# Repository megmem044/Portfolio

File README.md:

# Tic Tac Toe (Java)

A console based Tic Tac Toe game implemented using pure Java.  
The project follows a clean separation of concerns and includes basic tests without external frameworks.

## Features
- Two player console gameplay
- Turn based move handling
- Win detection for rows, columns, and diagonals
- Draw detection
- Board state rendering in console
- Reset and replay support
- Simple test coverage for core game logic

## Project Structure

tictactoe/
├── src/
│ └── com/app/tictactoe/
│ ├── Main.java
│ ├── Game.java
│ ├── Board.java
│ ├── Player.java
│ └── ConsoleUI.java
└── test/
└── com/app/tictactoe/
├── BoardTest.java
└── GameTest.java

## How to Compile

From the project root directory:
javac -d out src/com/app/tictactoe/.java test/com/app/tictactoe/.java

## How to Run Tests
java -cp out com.app.tictactoe.BoardTest
java -cp out com.app.tictactoe.GameTest

## How to Run the Game
java -cp out com.app.tictactoe.Main

## Notes
- No external libraries or frameworks are used
- Tests are written using plain Java assertions
- The project is structured to be easily extensible

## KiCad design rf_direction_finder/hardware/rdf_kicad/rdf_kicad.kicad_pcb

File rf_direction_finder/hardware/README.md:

# Hardware

This directory contains KiCAD hardware design files for the RF Direction Finder.

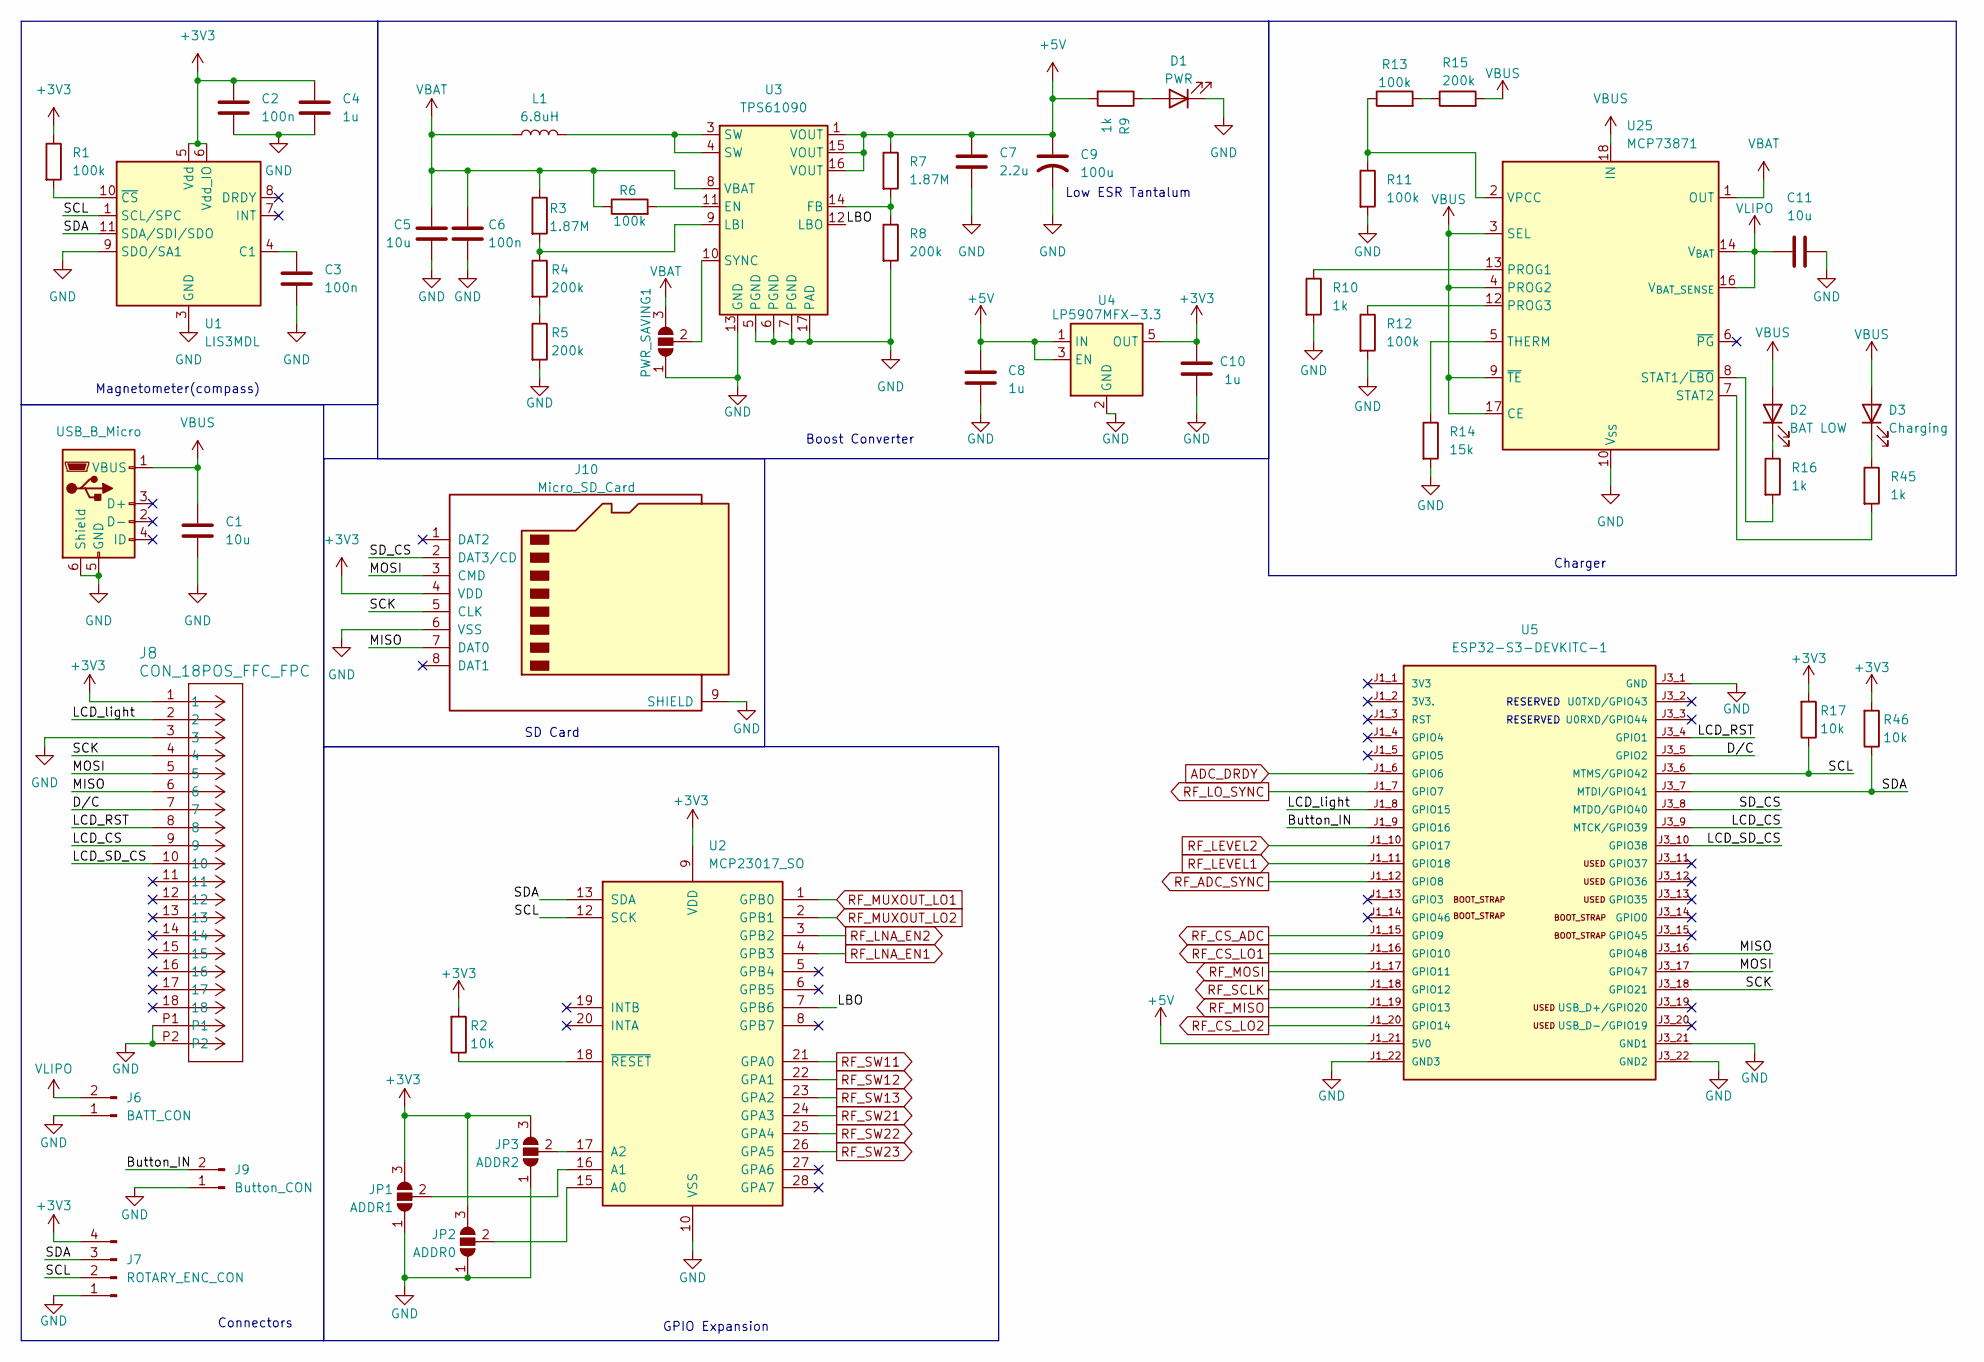
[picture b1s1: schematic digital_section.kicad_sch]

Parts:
C1, C5, C11: 10u; C_0603_1608Metric_Pad1.08x0.95mm_HandSolder
C2, C3, C6: 100n; C_0603_1608Metric_Pad1.08x0.95mm_HandSolder
C4, C8, C10: 1u; C_0603_1608Metric_Pad1.08x0.95mm_HandSolder
C7: 2.2u; C_0603_1608Metric_Pad1.08x0.95mm_HandSolder
C9: 100u; CP_EIA-3528-15_AVX-H_HandSolder
D1: PWR; LED_0603_1608Metric_Pad1.05x0.95mm_HandSolder
D2: BAT LOW; LED_0603_1608Metric_Pad1.05x0.95mm_HandSolder
D3: Charging; LED_0603_1608Metric_Pad1.05x0.95mm_HandSolder
J5: USB_B_Micro; USB_Micro-B_Amphenol_10118194-0001LF_Horizontal
J6: BATT_CON; PinHeader_1x02_P2.54mm_Vertical
J7: ROTARY_ENC_CON; PinHeader_1x04_P2.54mm_Vertical
J8: CON_18POS_FFC_FPC; CON_5051101892_MOL; Mfr_part 5051101892
J9: Button_CON; PinHeader_1x02_P2.54mm_Vertical
J10: Micro_SD_Card; microSD_HC_Molex_47219-2001
JP1: ADDR1; SolderJumper-3_P1.3mm_Open_RoundedPad1.0x1.5mm_NumberLabels
JP2: ADDR0; SolderJumper-3_P1.3mm_Open_RoundedPad1.0x1.5mm_NumberLabels
JP3: ADDR2; SolderJumper-3_P1.3mm_Open_RoundedPad1.0x1.5mm_NumberLabels
L1: 6.8uH; L_Sunlord_MWSA0412S
PWR_SAVING1: SolderJumper_3_Open; SolderJumper-3_P1.3mm_Open_RoundedPad1.0x1.5mm_NumberLabels
R1, R6, R11, R12, R13: 100k; R_0603_1608Metric_Pad0.98x0.95mm_HandSolder
R2, R17, R46: 10k; R_0603_1608Metric_Pad0.98x0.95mm_HandSolder
R3, R7: 1.87M; R_0603_1608Metric_Pad0.98x0.95mm_HandSolder
R4, R5, R8, R15: 200k; R_0603_1608Metric_Pad0.98x0.95mm_HandSolder
R9, R10, R16, R45: 1k; R_0603_1608Metric_Pad0.98x0.95mm_HandSolder
R14: 15k; R_0603_1608Metric_Pad0.98x0.95mm_HandSolder
U1: LIS3MDL; LGA-12_2x2mm_P0.5mm
U2: MCP23017_SO; SOIC-28W_7.5x17.9mm_P1.27mm
U3: TPS61090; Texas_RSA_VQFN-16-1EP_4x4mm_P0.65mm_EP2.7x2.7mm_ThermalVias
U4: LP5907MFX-3.3; SOT-23-5
U5: ESP32-S3-DEVKITC-1; ESP32-S3-DEVKITC-1-N8R8
U25: MCP73871; QFN-20-1EP_4x4mm_P0.5mm_EP2.5x2.5mm

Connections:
+3V3: C2.2, C4.2, C10.2, J7.4, J8.1, J10.4 (VDD), JP1.3 (B), JP2.3 (B), JP3.3 (B), R1.1, R2.2, R17.2, R46.2, U1.5 (Vdd), U1.6 (Vdd_IO), U2.9 (VDD), U4.5 (OUT); also elsewhere on the board
+5V: C7.2, C8.2, C9.1, R7.1, R9.2, U3.1 (VOUT), U3.15 (VOUT), U3.16 (VOUT), U4.1 (IN), U4.3 (EN), U5.J1_21 (5V0); also elsewhere on the board
/Digital Section/Button_IN: J9.2, U5.J1_9 (GPIO16)
/Digital Section/D/C: J8.7, U5.J3_5 (GPIO2)
/Digital Section/LBO: U2.7 (GPB6), U3.12 (LBO)
/Digital Section/LCD_CS: J8.9, U5.J3_9 (MTCK/GPIO39)
/Digital Section/LCD_RST: J8.8, U5.J3_4 (GPIO1)
/Digital Section/LCD_SD_CS: J8.10, U5.J3_10 (GPIO38)
/Digital Section/LCD_light: J8.2, U5.J1_8 (GPIO15)
/Digital Section/MISO: J8.6, J10.7 (DAT0), U5.J3_16 (GPIO48)
/Digital Section/MOSI: J8.5, J10.3 (CMD), U5.J3_17 (GPIO47)
/Digital Section/SCK: J8.4, J10.5 (CLK), U5.J3_18 (GPIO21)
/Digital Section/SCL: J7.2, R17.1, U1.1 (SCL/SPC), U2.12 (SCK), U5.J3_6 (MTMS/GPIO42)
/Digital Section/SDA: J7.3, R46.1, U1.11 (SDA/SDI/SDO), U2.13 (SDA), U5.J3_7 (MTDI/GPIO41)
/Digital Section/SD_CS: J10.2 (DAT3/CD), U5.J3_8 (MTDO/GPIO40)
ADC_DRDY: U5.J1_6 (GPIO6); also elsewhere on the board
GND: C1.1, C2.1, C3.1, C4.1, C5.1, C6.1, C7.1, C8.1, C9.2, C10.1, C11.1, D1.1 (K), J5.5 (GND), J5.6 (Shield), J6.1, J7.1, J8.3, J8.P1, J8.P2, J9.1, J10.6 (VSS), J10.9 (SHIELD), JP1.1 (A), JP2.1 (A), JP3.1 (A), PWR_SAVING1.1 (A), R5.2, R8.2, R10.2, R11.2, R12.2, R14.2, U1.2 (GND), U1.3 (GND), U1.9 (SDO/SA1), U1.12 (GND), U2.10 (VSS), U3.5 (PGND), U3.6 (PGND), U3.7 (PGND), U3.13 (GND), U3.17 (PAD), U4.2 (GND), U5.J1_22 (GND3), U5.J3_1 (GND), U5.J3_21 (GND1), U5.J3_22 (GND2), U25.10 (V_{SS}), U25.11 (V_{SS}), U25.21 (V_{SS}); also elsewhere on the board
unnamed: D1.2 (A), R9.1
unnamed: D2.1 (K), R16.1
unnamed: D3.1 (K), R45.1
unnamed: JP1.2 (C), U2.16 (A1)
unnamed: JP2.2 (C), U2.15 (A0)
unnamed: JP3.2 (C), U2.17 (A2)
unnamed: L1.2, U3.3 (SW), U3.4 (SW)
unnamed: PWR_SAVING1.2 (C), U3.10 (SYNC)
unnamed: R4.2, R5.1
unnamed: R13.2, R15.1
unnamed: C3.2, U1.4 (C1)
unnamed: R1.2, U1.10 (~CS)
unnamed: R2.1, U2.18 (~RESET)
unnamed: R6.2, U3.11 (EN)
unnamed: R7.2, R8.1, U3.14 (FB)
unnamed: R3.2, R4.1, U3.9 (LBI)
unnamed: R10.1, U25.13 (PROG1)
unnamed: R12.1, U25.12 (PROG3)
unnamed: R16.2, U25.8 (STAT1/~LBO)
unnamed: R45.2, U25.7 (STAT2)
unnamed: R14.1, U25.5 (THERM)
unnamed: R11.1, R13.1, U25.2 (VPCC)
RF_ADC_SYNC: U5.J1_12 (GPIO8); also elsewhere on the board
RF_CS_ADC: U5.J1_15 (GPIO9); also elsewhere on the board
RF_CS_LO1: U5.J1_16 (GPIO10); also elsewhere on the board
RF_CS_LO2: U5.J1_20 (GPIO14); also elsewhere on the board
RF_LEVEL1: U5.J1_11 (GPIO18); also elsewhere on the board
RF_LEVEL2: U5.J1_10 (GPIO17); also elsewhere on the board
RF_LNA_EN1: U2.4 (GPB3); also elsewhere on the board
RF_LNA_EN2: U2.3 (GPB2); also elsewhere on the board
RF_LO_SYNC: U5.J1_7 (GPIO7); also elsewhere on the board
RF_MISO: U5.J1_19 (GPIO13); also elsewhere on the board
RF_MOSI: U5.J1_17 (GPIO11); also elsewhere on the board
RF_MUXOUT_LO1: U2.1 (GPB0); also elsewhere on the board
RF_MUXOUT_LO2: U2.2 (GPB1); also elsewhere on the board
RF_SCLK: U5.J1_18 (GPIO12); also elsewhere on the board
RF_SW11: U2.21 (GPA0); also elsewhere on the board
RF_SW12: U2.22 (GPA1); also elsewhere on the board
RF_SW13: U2.23 (GPA2)
RF_SW21: U2.24 (GPA3); also elsewhere on the board
RF_SW22: U2.25 (GPA4); also elsewhere on the board
RF_SW23: U2.26 (GPA5)
VBAT: C5.2, C6.2, L1.1, PWR_SAVING1.3 (B), R3.1, R6.1, U3.8 (VBAT), U25.1 (OUT), U25.20 (OUT)
VBUS: C1.2, D2.2 (A), D3.2 (A), J5.1 (VBUS), R15.2, U25.3 (SEL), U25.4 (PROG2), U25.9 (~TE), U25.17 (CE), U25.18 (IN), U25.19 (IN)
VLIPO: C11.2, J6.2, U25.14 (V_{BAT}), U25.15 (V_{BAT}), U25.16 (V_{BAT_SENSE})

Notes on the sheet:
Boost Converter
RESERVED
Connectors
Charger
SD Card
Magnetometer(compass)
Low ESR Tantalum
GPIO Expansion

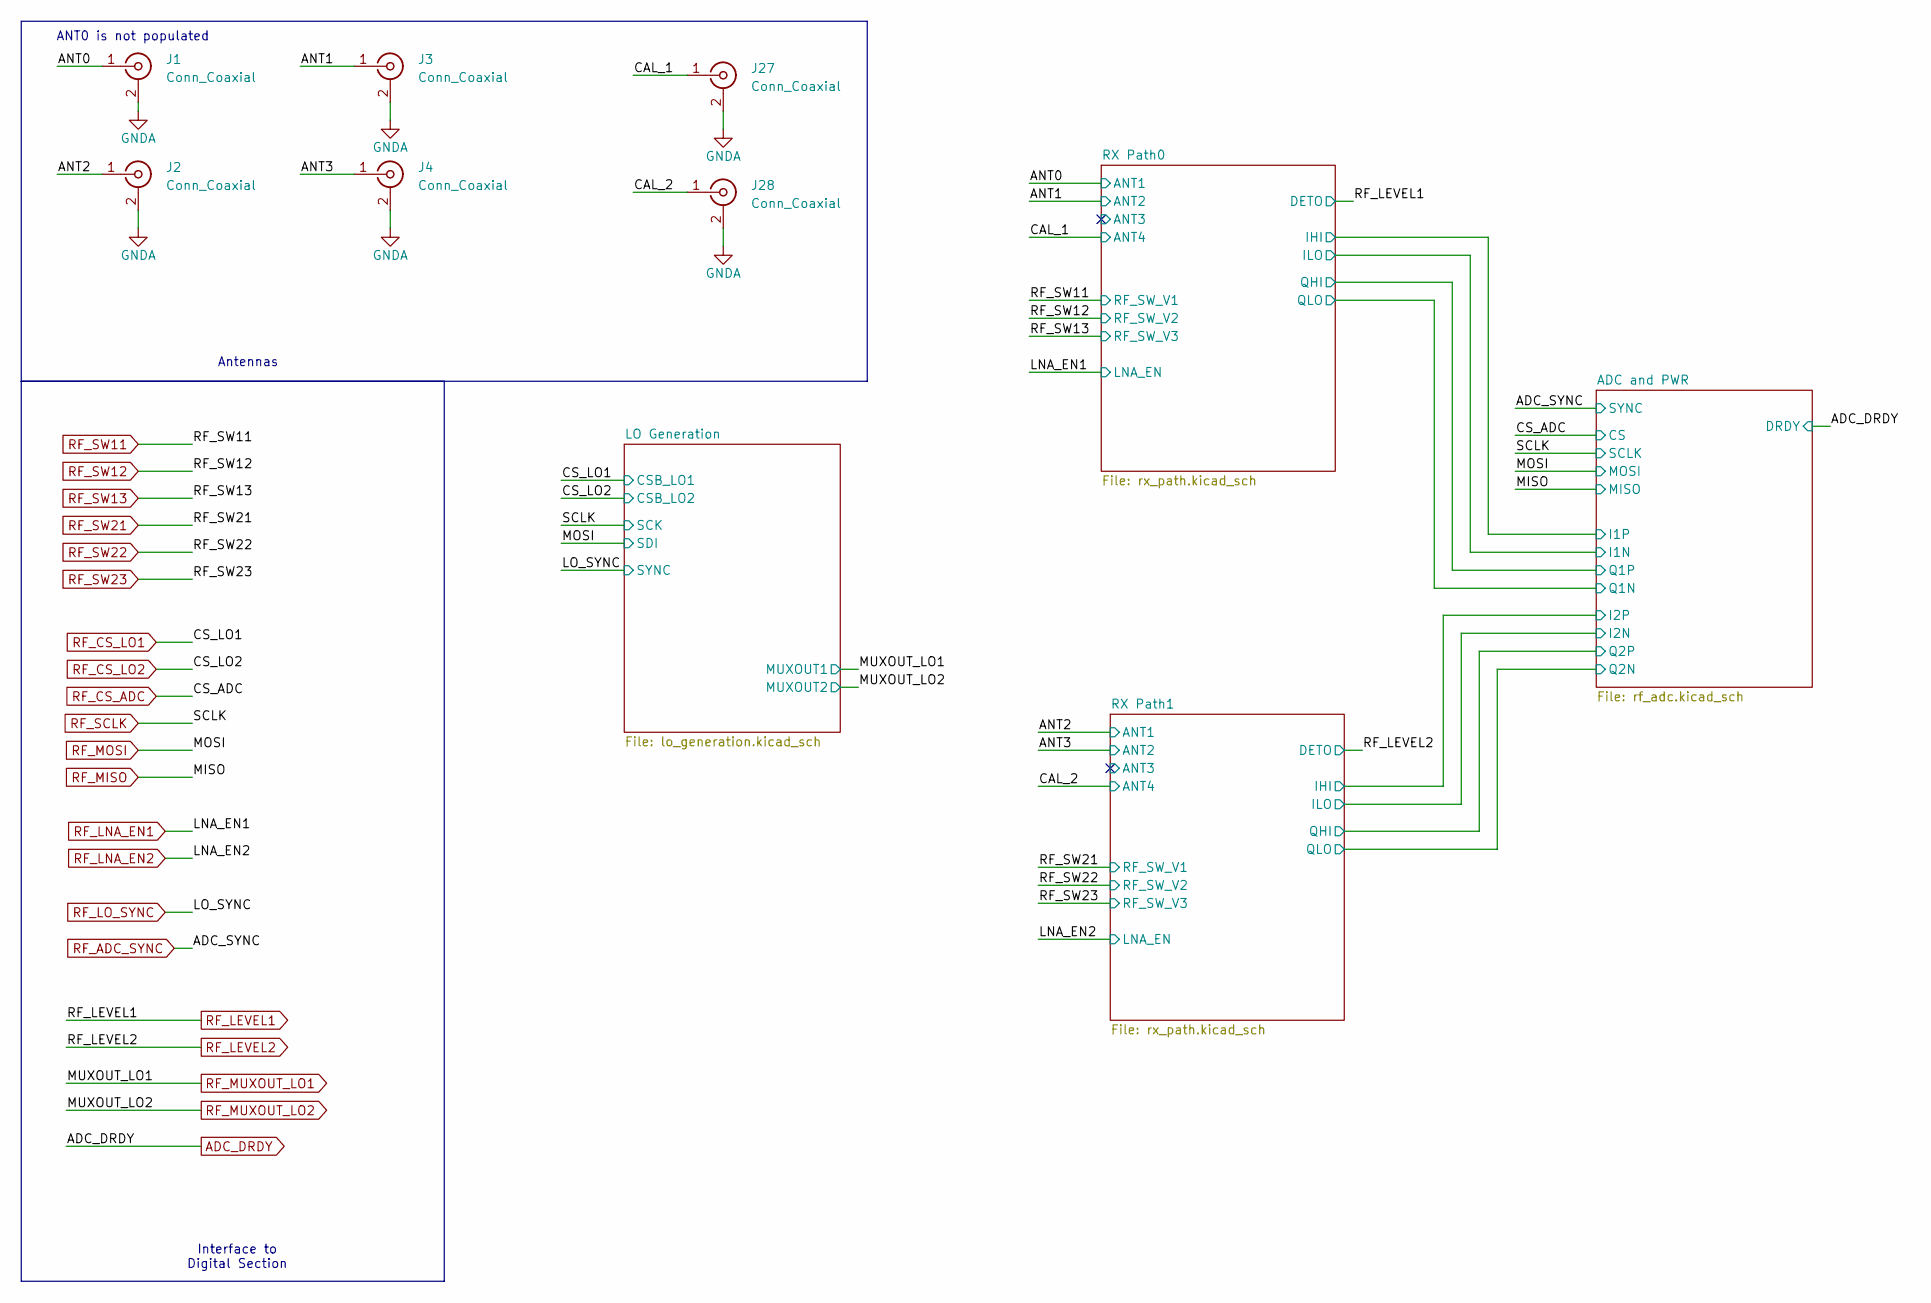
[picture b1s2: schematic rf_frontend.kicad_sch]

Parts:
J1, J2, J3, J4, J27, J28: Conn_Coaxial; U.FL_Molex_MCRF_73412-0110_Vertical

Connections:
/RF Frontend/ANT0: J1.1 (In); also elsewhere on the board
/RF Frontend/ANT1: J3.1 (In); also elsewhere on the board
/RF Frontend/ANT2: J2.1 (In); also elsewhere on the board
/RF Frontend/ANT3: J4.1 (In); also elsewhere on the board
/RF Frontend/CAL_1: J27.1 (In); also elsewhere on the board
/RF Frontend/CAL_2: J28.1 (In); also elsewhere on the board
GND: J1.2 (Ext), J2.2 (Ext), J3.2 (Ext), J4.2 (Ext), J27.2 (Ext), J28.2 (Ext); also elsewhere on the board

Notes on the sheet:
Antennas
Interface to Digital Section
ANT0 is not populated

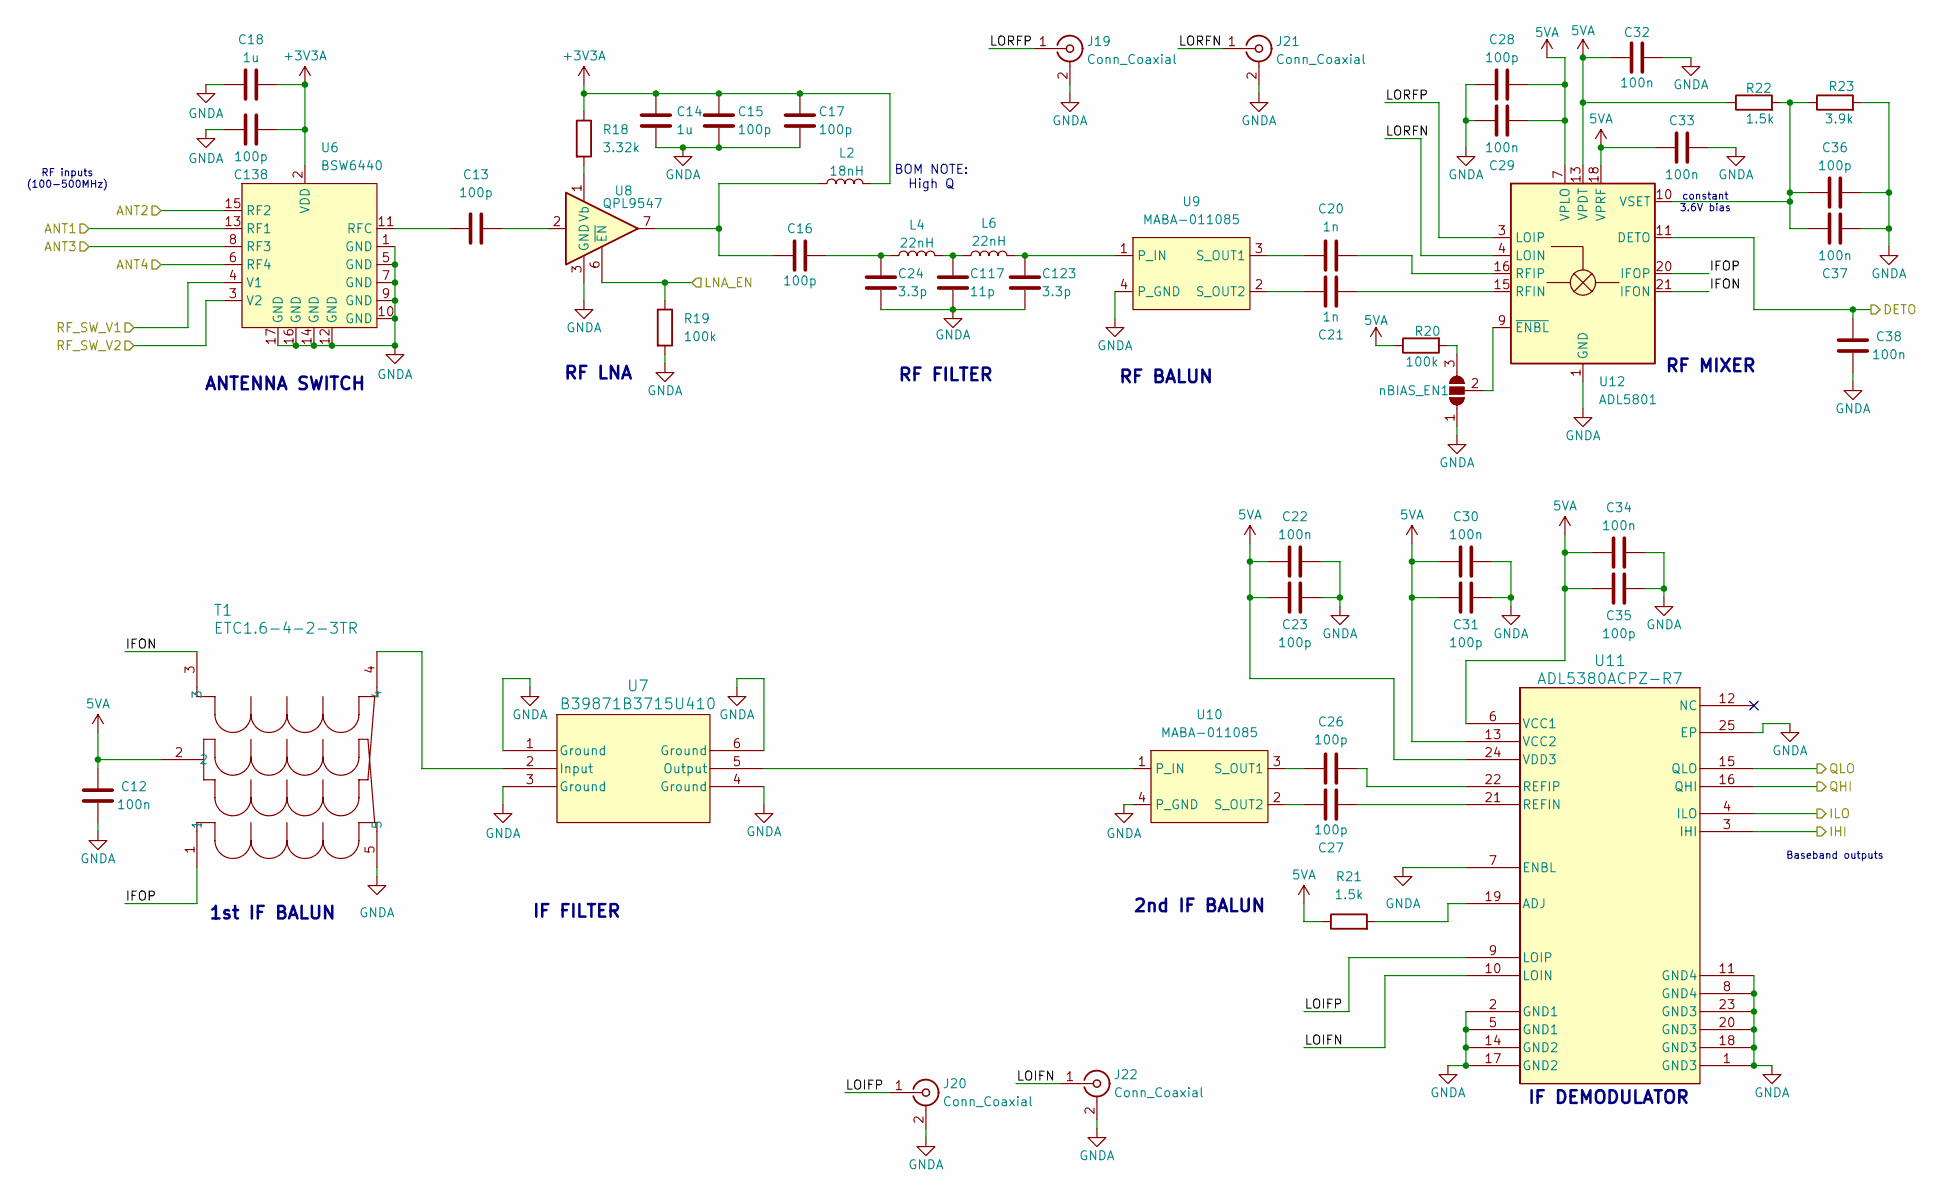
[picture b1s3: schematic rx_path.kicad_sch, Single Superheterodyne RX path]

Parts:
C12, C22, C29, C30, C32, C33, C34, C37, C38: 100n; C_0603_1608Metric_Pad1.08x0.95mm_HandSolder
C13, C16, C26, C27: 100p; C_0402_1005Metric
C14, C18: 1u; C_0603_1608Metric_Pad1.08x0.95mm_HandSolder
C15, C17, C23, C28, C31, C35, C36, C138: 100p; C_0603_1608Metric_Pad1.08x0.95mm_HandSolder
C20, C21: 1n; C_0402_1005Metric
C24, C123: 3.3p; C_0402_1005Metric
C117: 11p; C_0402_1005Metric
J19, J20, J21, J22: Conn_Coaxial; U.FL_Molex_MCRF_73412-0110_Vertical
L2: 18nH; L_0402_1005Metric
L4, L6: 22nH; L_0402_1005Metric
R18: 3.32k; R_0603_1608Metric_Pad0.98x0.95mm_HandSolder
R19, R20: 100k; R_0603_1608Metric_Pad0.98x0.95mm_HandSolder
R21, R22: 1.5k; R_0603_1608Metric_Pad0.98x0.95mm_HandSolder
R23: 3.9k; R_0603_1608Metric_Pad0.98x0.95mm_HandSolder
T1: ETC1.6-4-2-3TR; ETC1.6-4-2-3TR_MCM
U6: BSW6440
U7: B39871B3715U410
U8: QPL9547; DFN-8-1EP_2x2mm_P0.5mm_EP0.8x1.6mm
U9, U10: MABA-011085; SMD-4P_7.1x6.4mm
U11: ADL5380ACPZ-R7
U12: ADL5801; ADL5801_LFCSP-VQ-24-1EP_4x4mm_P0.5mm_EP2.642x2.642mm
nBIAS_EN1: SolderJumper_3_Open; SolderJumper-3_P1.3mm_Open_RoundedPad1.0x1.5mm_NumberLabels

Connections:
+3V3A: C14.2, C15.2, C17.2, C18.2, C138.2, L2.2, R18.1, U6.2 (VDD); also elsewhere on the board
+5VA: C12.2, C22.2, C23.2, C28.2, C29.2, C30.2, C31.2, C32.1, C33.1, C34.2, C35.2, R20.1, R21.1, R22.1, T1.2, U11.6 (VCC1), U11.13 (VCC2), U11.24 (VDD3), U12.7 (VPLO), U12.13 (VPDT), U12.18 (VPRF), U12.24 (VPLO); also elsewhere on the board
/RF Frontend/ADC and PWR/I1N: U11.4 (ILO); also elsewhere on the board
/RF Frontend/ADC and PWR/I1P: U11.3 (IHI); also elsewhere on the board
/RF Frontend/ADC and PWR/Q1N: U11.15 (QLO); also elsewhere on the board
/RF Frontend/ADC and PWR/Q1P: U11.16 (QHI); also elsewhere on the board
/RF Frontend/ANT0: U6.13 (RF1); also elsewhere on the board
/RF Frontend/ANT1: U6.15 (RF2); also elsewhere on the board
/RF Frontend/CAL_1: U6.6 (RF4); also elsewhere on the board
/RF Frontend/RX Path0/ANT3: U6.8 (RF3)
/RF Frontend/RX Path0/IFON: T1.3, U12.21 (IFON)
/RF Frontend/RX Path0/IFOP: T1.1, U12.20 (IFOP)
/RF Frontend/RX Path0/LOIFN: J22.1 (In), U11.10 (LOIN)
/RF Frontend/RX Path0/LOIFP: J20.1 (In), U11.9 (LOIP)
/RF Frontend/RX Path0/LORFN: J21.1 (In), U12.4 (LOIN)
/RF Frontend/RX Path0/LORFP: J19.1 (In), U12.3 (LOIP)
GND: C12.1, C14.1, C15.1, C17.1, C18.1, C22.1, C23.1, C24.2, C28.1, C29.1, C30.1, C31.1, C32.2, C33.2, C34.1, C35.1, C36.1, C37.1, C38.1, C117.2, C123.2, C138.1, J19.2 (Ext), J20.2 (Ext), J21.2 (Ext), J22.2 (Ext), R19.2, R23.2, T1.5, U6.1 (GND), U6.5 (GND), U6.7 (GND), U6.9 (GND), U6.10 (GND), U6.12 (GND), U6.14 (GND), U6.16 (GND), U6.17 (GND), U7.1 (Ground), U7.3 (Ground), U7.4 (Ground), U7.6 (Ground), U8.3 (GND), U8.4 (GND), U8.5 (GND), U8.8 (GND), U8.9 (GND), U9.4 (P_GND), U10.4 (P_GND), U11.1 (GND3), U11.2 (GND1), U11.5 (GND1), U11.7 (ENBL), U11.8 (GND4), U11.11 (GND4), U11.14 (GND2), U11.17 (GND2), U11.18 (GND3), U11.20 (GND3), U11.23 (GND3), U11.25 (EP), U12.1 (GND), U12.2 (GND), U12.5 (GND), U12.6 (GND), U12.8 (GND), U12.12 (GND), U12.14 (GND), U12.17 (GND), U12.19 (GND), U12.23 (GND), U12.25 (GND), nBIAS_EN1.1 (A); also elsewhere on the board
unnamed: C13.2, U8.2
unnamed: C16.1, L2.1, U8.7
unnamed: C16.2, C24.1, L4.1
unnamed: C117.1, L4.2, L6.1
unnamed: C13.1, U6.11 (RFC)
unnamed: T1.4, U7.2 (Input)
unnamed: R18.2, U8.1 (Vb)
unnamed: C123.1, L6.2, U9.1 (P_IN)
unnamed: C20.1, U9.3 (S_OUT1)
unnamed: C21.2, U9.2 (S_OUT2)
unnamed: U7.5 (Output), U10.1 (P_IN)
unnamed: C26.1, U10.3 (S_OUT1)
unnamed: C27.2, U10.2 (S_OUT2)
unnamed: R21.2, U11.19 (ADJ)
unnamed: C27.1, U11.21 (REFIN)
unnamed: C26.2, U11.22 (REFIP)
unnamed: C21.1, U12.15 (RFIN)
unnamed: C20.2, U12.16 (RFIP)
unnamed: C36.2, C37.2, R22.2, R23.1, U12.10 (VSET)
unnamed: U12.9 (~ENBL), nBIAS_EN1.2 (C)
unnamed: R20.2, nBIAS_EN1.3 (B)
RF_LEVEL1: C38.2, U12.11 (DETO); also elsewhere on the board
RF_LNA_EN1: R19.1, U8.6 (~EN); also elsewhere on the board
RF_SW11: U6.4 (V1); also elsewhere on the board
RF_SW12: U6.3 (V2); also elsewhere on the board

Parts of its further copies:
C19, C113: 1u; C_0603_1608Metric_Pad1.08x0.95mm_HandSolder
C25, C124: 3.3p; C_0402_1005Metric
C111, C121, C128, C129, C131, C132, C133, C136, C137: 100n; C_0603_1608Metric_Pad1.08x0.95mm_HandSolder
C112, C115, C125, C126: 100p; C_0402_1005Metric
C114, C116, C122, C127, C130, C134, C135, C139: 100p; C_0603_1608Metric_Pad1.08x0.95mm_HandSolder
C118: 11p; C_0402_1005Metric
C119, C120: 1n; C_0402_1005Metric
J23, J24, J25, J26: Conn_Coaxial; U.FL_Molex_MCRF_73412-0110_Vertical
L3: 18nH; L_0402_1005Metric
L5, L7: 22nH; L_0402_1005Metric
R39: 3.32k; R_0603_1608Metric_Pad0.98x0.95mm_HandSolder
R40, R41: 100k; R_0603_1608Metric_Pad0.98x0.95mm_HandSolder
R42, R43: 1.5k; R_0603_1608Metric_Pad0.98x0.95mm_HandSolder
R44: 3.9k; R_0603_1608Metric_Pad0.98x0.95mm_HandSolder
T2: ETC1.6-4-2-3TR; ETC1.6-4-2-3TR_MCM
U18: BSW6440
U19: B39871B3715U410
U20: QPL9547; DFN-8-1EP_2x2mm_P0.5mm_EP0.8x1.6mm
U21, U22: MABA-011085; SMD-4P_7.1x6.4mm
U23: ADL5380ACPZ-R7
U24: ADL5801; ADL5801_LFCSP-VQ-24-1EP_4x4mm_P0.5mm_EP2.642x2.642mm
nBIAS_EN2: SolderJumper_3_Open; SolderJumper-3_P1.3mm_Open_RoundedPad1.0x1.5mm_NumberLabels

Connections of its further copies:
+3V3A: C19.2, C113.2, C114.2, C116.2, C139.2, L3.2, R39.1, U18.2 (VDD); also elsewhere on the board
+5VA: C111.2, C121.2, C122.2, C127.2, C128.2, C129.2, C130.2, C131.1, C132.1, C133.2, C134.2, R41.1, R42.1, R43.1, T2.2, U23.6 (VCC1), U23.13 (VCC2), U23.24 (VDD3), U24.7 (VPLO), U24.13 (VPDT), U24.18 (VPRF), U24.24 (VPLO); also elsewhere on the board
/RF Frontend/ADC and PWR/I2N: U23.4 (ILO); also elsewhere on the board
/RF Frontend/ADC and PWR/I2P: U23.3 (IHI); also elsewhere on the board
/RF Frontend/ADC and PWR/Q2N: U23.15 (QLO); also elsewhere on the board
/RF Frontend/ADC and PWR/Q2P: U23.16 (QHI); also elsewhere on the board
/RF Frontend/ANT2: U18.13 (RF1); also elsewhere on the board
/RF Frontend/ANT3: U18.15 (RF2); also elsewhere on the board
/RF Frontend/CAL_2: U18.6 (RF4); also elsewhere on the board
/RF Frontend/RX Path1/ANT3: U18.8 (RF3)
/RF Frontend/RX Path1/IFON: T2.3, U24.21 (IFON)
/RF Frontend/RX Path1/IFOP: T2.1, U24.20 (IFOP)
/RF Frontend/RX Path1/LOIFN: J26.1 (In), U23.10 (LOIN)
/RF Frontend/RX Path1/LOIFP: J24.1 (In), U23.9 (LOIP)
/RF Frontend/RX Path1/LORFN: J25.1 (In), U24.4 (LOIN)
/RF Frontend/RX Path1/LORFP: J23.1 (In), U24.3 (LOIP)
GND: C19.1, C25.2, C111.1, C113.1, C114.1, C116.1, C118.2, C121.1, C122.1, C124.2, C127.1, C128.1, C129.1, C130.1, C131.2, C132.2, C133.1, C134.1, C135.1, C136.1, C137.1, C139.1, J23.2 (Ext), J24.2 (Ext), J25.2 (Ext), J26.2 (Ext), R40.2, R44.2, T2.5, U18.1 (GND), U18.5 (GND), U18.7 (GND), U18.9 (GND), U18.10 (GND), U18.12 (GND), U18.14 (GND), U18.16 (GND), U18.17 (GND), U19.1 (Ground), U19.3 (Ground), U19.4 (Ground), U19.6 (Ground), U20.3 (GND), U20.4 (GND), U20.5 (GND), U20.8 (GND), U20.9 (GND), U21.4 (P_GND), U22.4 (P_GND), U23.1 (GND3), U23.2 (GND1), U23.5 (GND1), U23.7 (ENBL), U23.8 (GND4), U23.11 (GND4), U23.14 (GND2), U23.17 (GND2), U23.18 (GND3), U23.20 (GND3), U23.23 (GND3), U23.25 (EP), U24.1 (GND), U24.2 (GND), U24.5 (GND), U24.6 (GND), U24.8 (GND), U24.12 (GND), U24.14 (GND), U24.17 (GND), U24.19 (GND), U24.23 (GND), U24.25 (GND), nBIAS_EN2.1 (A); also elsewhere on the board
unnamed: C112.2, U20.2
unnamed: C115.1, L3.1, U20.7
unnamed: C25.1, C115.2, L5.1
unnamed: C118.1, L5.2, L7.1
unnamed: C112.1, U18.11 (RFC)
unnamed: T2.4, U19.2 (Input)
unnamed: U19.5 (Output), U22.1 (P_IN)
unnamed: R39.2, U20.1 (Vb)
unnamed: C124.1, L7.2, U21.1 (P_IN)
unnamed: C119.1, U21.3 (S_OUT1)
unnamed: C120.2, U21.2 (S_OUT2)
unnamed: C125.1, U22.3 (S_OUT1)
unnamed: C126.2, U22.2 (S_OUT2)
unnamed: R42.2, U23.19 (ADJ)
unnamed: C126.1, U23.21 (REFIN)
unnamed: C125.2, U23.22 (REFIP)
unnamed: C120.1, U24.15 (RFIN)
unnamed: C119.2, U24.16 (RFIP)
unnamed: C135.2, C136.2, R43.2, R44.1, U24.10 (VSET)
unnamed: U24.9 (~ENBL), nBIAS_EN2.2 (C)
unnamed: R41.2, nBIAS_EN2.3 (B)
RF_LEVEL2: C137.2, U24.11 (DETO); also elsewhere on the board
RF_LNA_EN2: R40.1, U20.6 (~EN); also elsewhere on the board
RF_SW21: U18.4 (V1); also elsewhere on the board
RF_SW22: U18.3 (V2); also elsewhere on the board

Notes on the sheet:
1st IF BALUN
RF LNA
ANTENNA SWITCH
IF FILTER
RF FILTER
2nd IF BALUN
IF DEMODULATOR
RF MIXER
RF BALUN
BOM NOTE: High Q
RF inputs (100-500MHz)
Baseband outputs
constant 3.6V bias

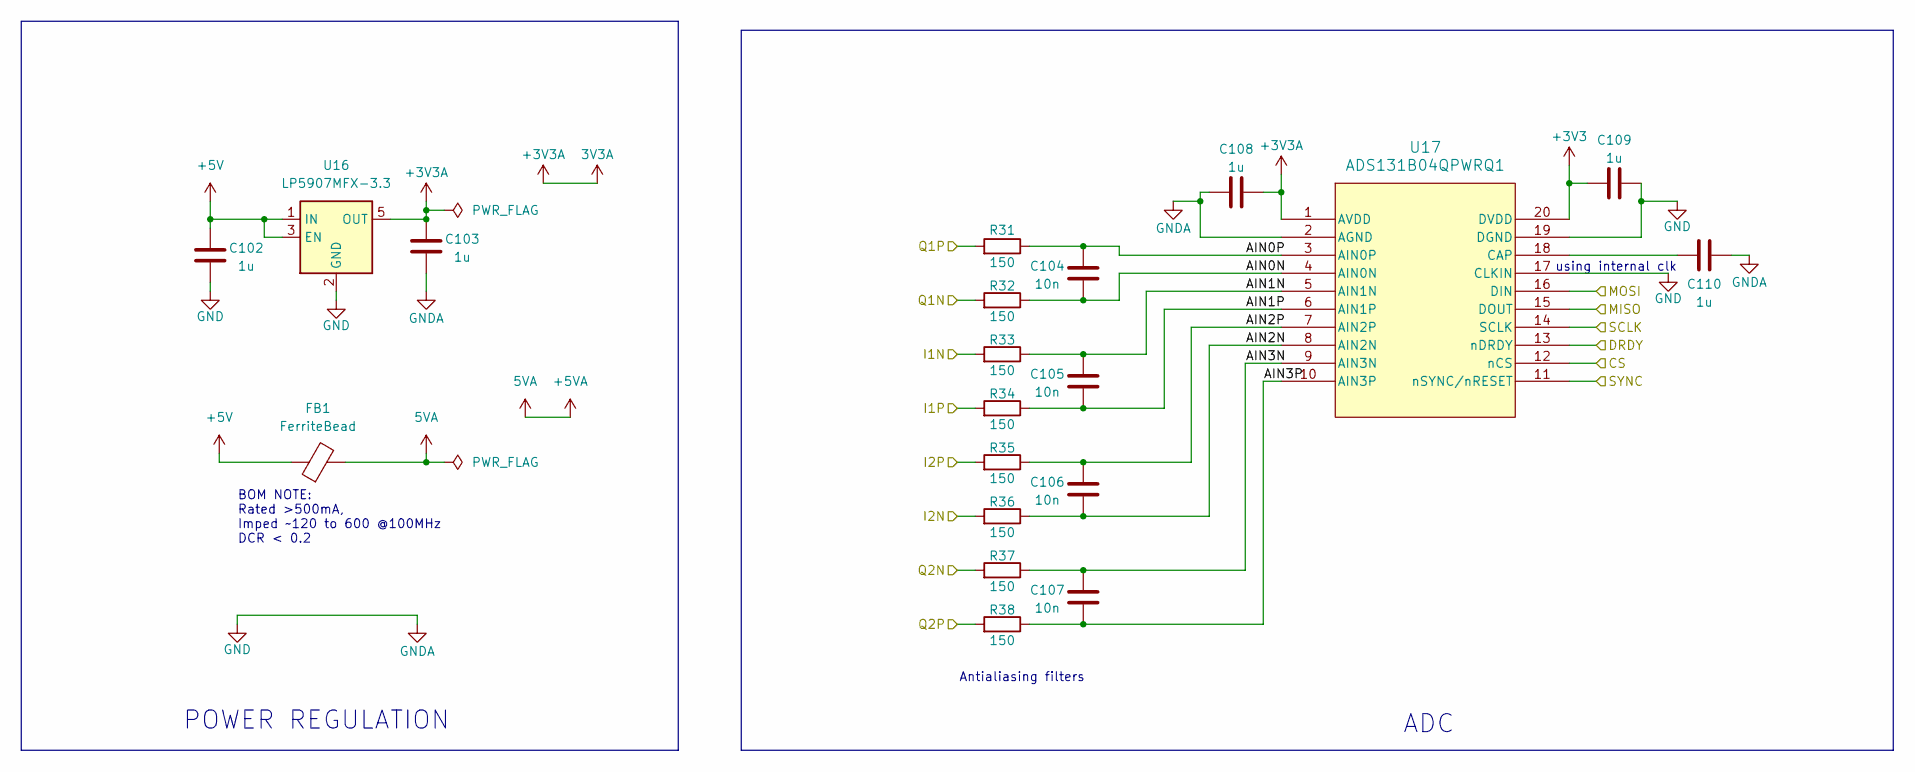
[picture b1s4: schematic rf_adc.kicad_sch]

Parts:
C102, C103, C108, C109, C110: 1u; C_0603_1608Metric_Pad1.08x0.95mm_HandSolder
C104, C105, C106, C107: 10n; C_0603_1608Metric_Pad1.08x0.95mm_HandSolder
FB1: FerriteBead; C_0603_1608Metric
R31, R32, R33, R34, R35, R36, R37, R38: 150; R_0603_1608Metric_Pad0.98x0.95mm_HandSolder
U16: LP5907MFX-3.3; SOT-23-5
U17: ADS131B04QPWRQ1

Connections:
+3V3: C109.2, U17.20 (DVDD); also elsewhere on the board
+3V3A: C103.2, C108.1, U16.5 (OUT), U17.1 (AVDD); also elsewhere on the board
+5V: C102.2, FB1.1, U16.1 (IN), U16.3 (EN); also elsewhere on the board
+5VA: FB1.2; also elsewhere on the board
/RF Frontend/ADC and PWR/AIN0N: C104.2, R32.1, U17.4 (AIN0N)
/RF Frontend/ADC and PWR/AIN0P: C104.1, R31.1, U17.3 (AIN0P)
/RF Frontend/ADC and PWR/AIN1N: C105.1, R33.1, U17.5 (AIN1N)
/RF Frontend/ADC and PWR/AIN1P: C105.2, R34.1, U17.6 (AIN1P)
/RF Frontend/ADC and PWR/AIN2N: C106.2, R36.1, U17.8 (AIN2N)
/RF Frontend/ADC and PWR/AIN2P: C106.1, R35.1, U17.7 (AIN2P)
/RF Frontend/ADC and PWR/AIN3N: C107.1, R37.1, U17.9 (AIN3N)
/RF Frontend/ADC and PWR/AIN3P: C107.2, R38.1, U17.10 (AIN3P)
/RF Frontend/ADC and PWR/I1N: R33.2; also elsewhere on the board
/RF Frontend/ADC and PWR/I1P: R34.2; also elsewhere on the board
/RF Frontend/ADC and PWR/I2N: R36.2; also elsewhere on the board
/RF Frontend/ADC and PWR/I2P: R35.2; also elsewhere on the board
/RF Frontend/ADC and PWR/Q1N: R32.2; also elsewhere on the board
/RF Frontend/ADC and PWR/Q1P: R31.2; also elsewhere on the board
/RF Frontend/ADC and PWR/Q2N: R37.2; also elsewhere on the board
/RF Frontend/ADC and PWR/Q2P: R38.2; also elsewhere on the board
ADC_DRDY: U17.13 (nDRDY); also elsewhere on the board
GND: C102.1, C103.1, C108.2, C109.1, C110.1, U16.2 (GND), U17.2 (AGND), U17.17 (CLKIN), U17.19 (DGND); also elsewhere on the board
unnamed: C110.2, U17.18 (CAP)
RF_ADC_SYNC: U17.11 (nSYNC/nRESET); also elsewhere on the board
RF_CS_ADC: U17.12 (nCS); also elsewhere on the board
RF_MISO: U17.15 (DOUT); also elsewhere on the board
RF_MOSI: U17.16 (DIN); also elsewhere on the board
RF_SCLK: U17.14 (SCLK); also elsewhere on the board

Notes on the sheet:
using internal clk
Antialiasing filters
BOM NOTE: Rated >500mA, Imped ~120 to 600 @100MHz DCR < 0.2
ADC
POWER REGULATION
